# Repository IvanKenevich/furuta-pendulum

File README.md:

# furuta-pendulum

Inverted rotary pendulum

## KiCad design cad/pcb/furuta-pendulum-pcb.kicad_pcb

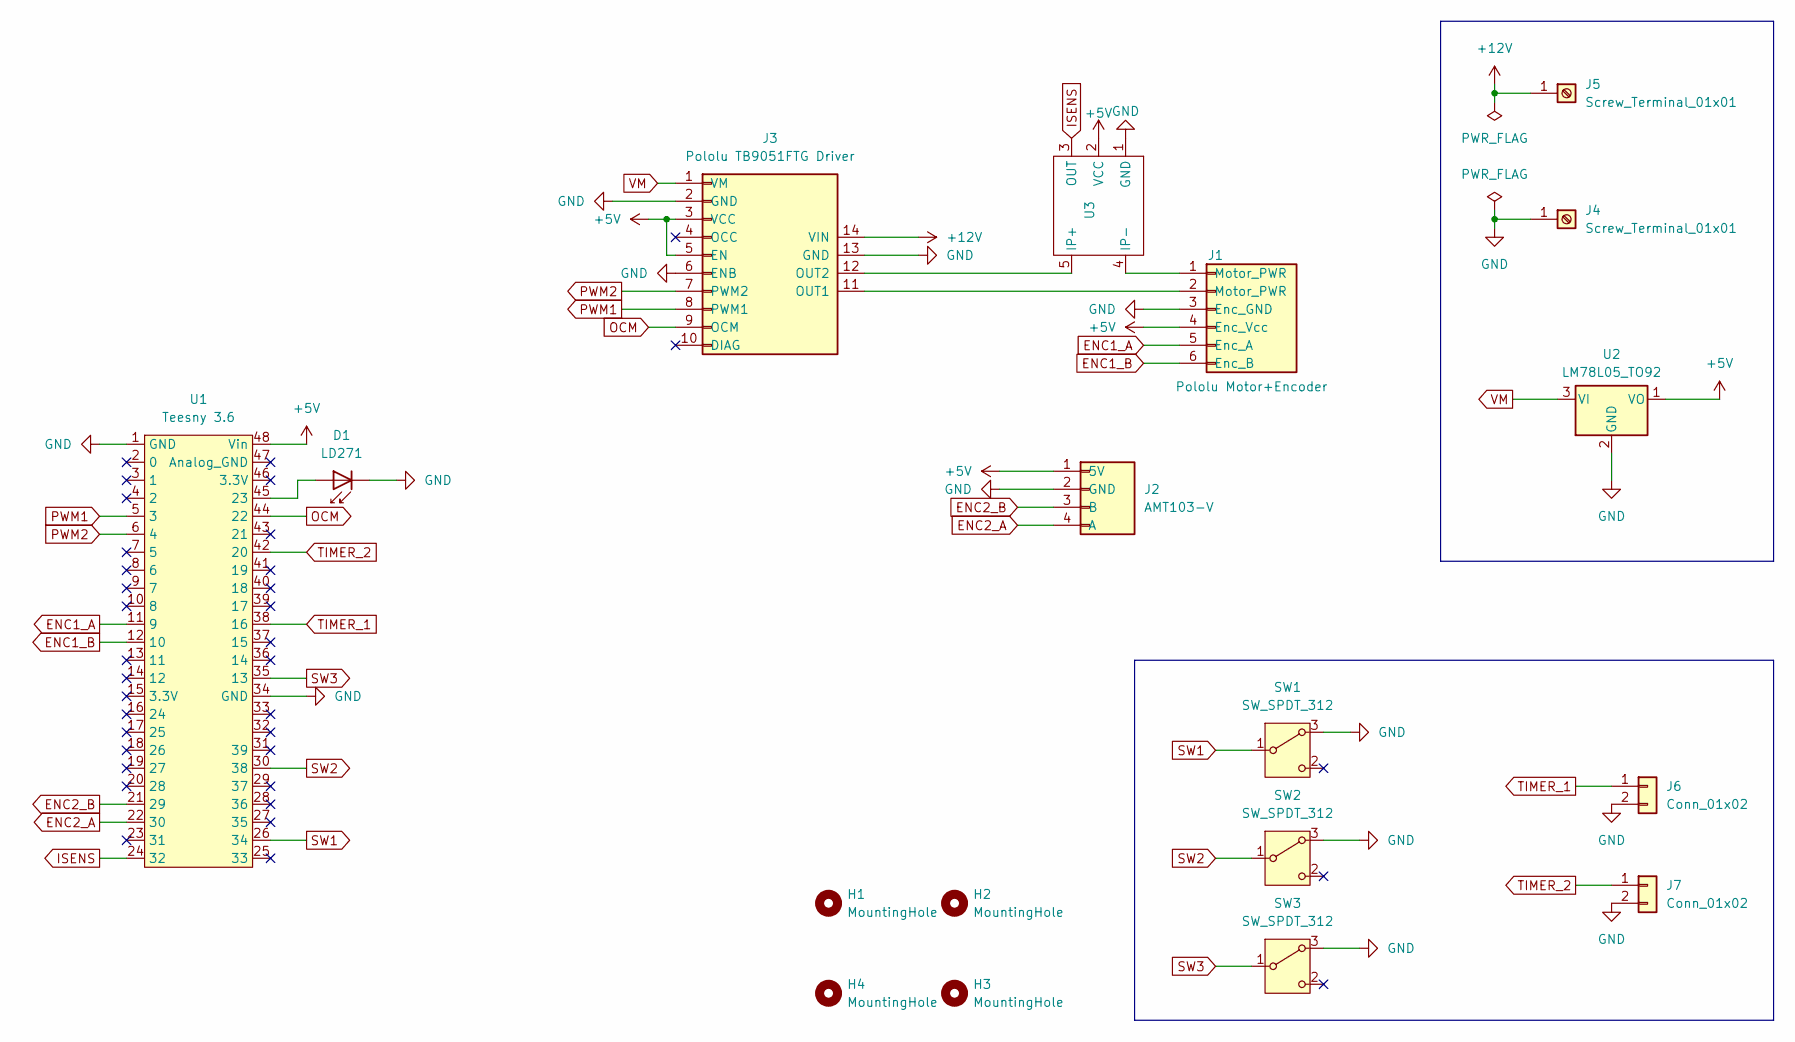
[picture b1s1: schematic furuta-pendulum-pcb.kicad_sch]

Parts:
D1: LD271; LED_D5.0mm_IRGrey
H1, H2, H3, H4: MountingHole; MountingHole_2.2mm_M2
J1: Pololu Motor+Encoder; PinHeader_1x06_P2.54mm_Vertical
J2: AMT103-V; PinSocket_1x04_P2.54mm_Vertical
J3: Pololu TB9051FTG Driver; Pololu TB9051FTG motor driver
J4, J5: Screw_Terminal_01x01; CalTest_CT3151
J6, J7: Conn_01x02; PinHeader_1x02_P2.54mm_Vertical
SW1, SW2, SW3: SW_SPDT_312; Flat Toggle Switch
U1: Teesny 3.6; Teensy 3.6
U2: LM78L05_TO92; TO-92_Inline
U3: Pololu ACS724 Current Sensor

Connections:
+5V: J1.4 (Enc_Vcc), J2.1 (5V), J3.3 (VCC), J3.5 (EN), U1.48 (Vin), U2.1 (VO), U3.2 (VCC)
+12V: J3.14 (VIN), J5.1
ENC1_A: J1.5 (Enc_A), U1.11 (9)
ENC1_B: J1.6 (Enc_B), U1.12 (10)
ENC2_A: J2.4 (A), U1.22 (30)
ENC2_B: J2.3 (B), U1.21 (29)
GND: D1.1 (K), J1.3 (Enc_GND), J2.2 (GND), J3.2 (GND), J3.6 (ENB), J3.13 (GND), J4.1, J6.2, J7.2, SW1.3 (A), SW2.3 (A), SW3.3 (A), U1.1 (GND), U1.34 (GND), U2.2 (GND), U3.1 (GND)
ISENS: U1.24 (32), U3.3 (OUT)
unnamed: D1.2 (A), U1.45 (23)
unnamed: J1.2 (Motor_PWR), J3.11 (OUT1)
unnamed: J3.12 (OUT2), U3.5 (IP+)
unnamed: J1.1 (Motor_PWR), U3.4 (IP-)
OCM: J3.9 (OCM), U1.44 (22)
PWM1: J3.8 (PWM1), U1.5 (3)
PWM2: J3.7 (PWM2), U1.6 (4)
SW1: SW1.1 (B), U1.26 (34)
SW2: SW2.1 (B), U1.30 (38)
SW3: SW3.1 (B), U1.35 (13)
TIMER_1: J6.1, U1.38 (16)
TIMER_2: J7.1, U1.42 (20)
VM: J3.1 (VM), U2.3 (VI)

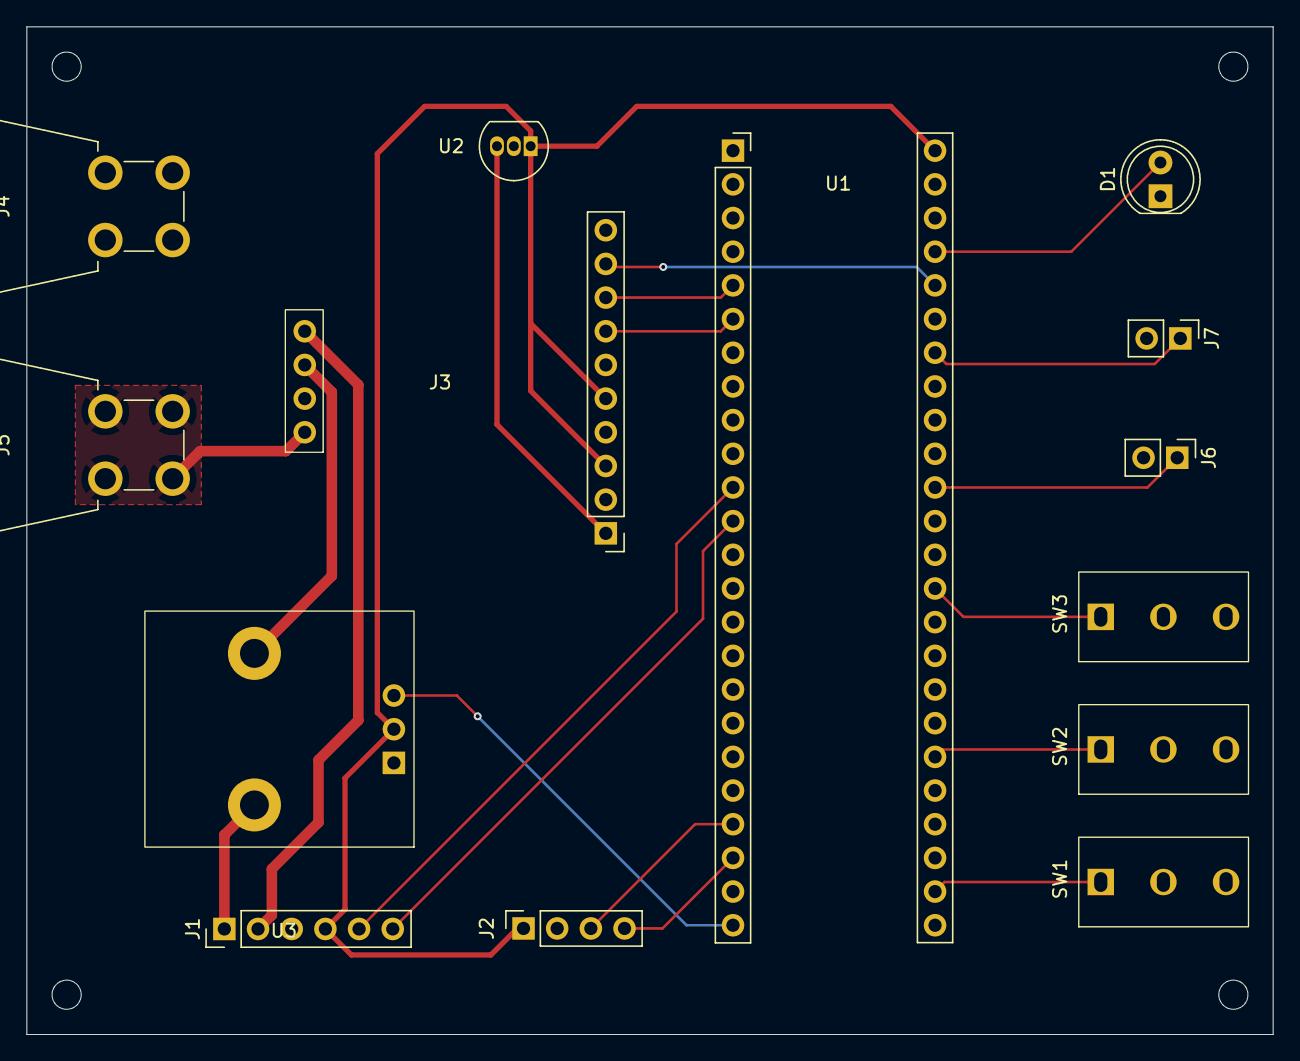
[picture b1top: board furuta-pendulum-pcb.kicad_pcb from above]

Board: 2 copper layers, 94.0 x 76.0 mm, 18 parts (0 on the bottom side), 21 nets.

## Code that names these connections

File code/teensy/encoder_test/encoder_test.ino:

#include <Encoder.h>

#define rad2deg (180.0 / M_PI)
#define deg2rad (M_PI / 180.0)

//#define LED_BUILTIN 13
#define PIN_ENC1_A   2
#define PIN_ENC1_B   3
#define PIN_TIMER_1   32
#define PIN_TIMER_2   31
#define PIN_PWM1    29
#define PIN_PWM2    30
#define PIN_SW_1    33
#define PIN_SW_2    39
#define PIN_SW_3    15

#define TIMER_CYCLE_MICROS 1 * 100
const float Ts = 1e-6 * TIMER_CYCLE_MICROS;
IntervalTimer t1;
const float input_freq = 4, // Hz
            input_amp  = 5, // V
            supply_voltage = 12; // V
const int pos_buff_size = 50; // samples
unsigned long i = 0;

Encoder enc1(PIN_ENC1_A, PIN_ENC1_B),
        enc2(PIN_ENC2_A, PIN_ENC2_B);
volatile long enc1_pos_raw, enc2_pos_raw;
volatile float enc1_pos, enc2_pos, enc2_speed;
float enc2_pos_buff[pos_buff_size] = {0};

volatile char timer1_pin_state = 0, timer2_pin_state = 0;
volatile float pwm_out = 0, pwm_out_copy = 0, error = 0, setpoint = 0, integral = 0;
volatile int motor_enabled = false, integral_enabled = false;


void setup() {
  pinMode(LED_BUILTIN, OUTPUT);
  digitalWrite(LED_BUILTIN, HIGH);

  pinMode(PIN_TIMER_1, OUTPUT);
  pinMode(PIN_TIMER_2, OUTPUT);
  pinMode(PIN_SW_1, INPUT);
  pinMode(PIN_SW_2, INPUT);
  pinMode(PIN_SW_3, INPUT);

  Serial.begin(57600);
  
  t1.begin(isr_t1, TIMER_CYCLE_MICROS);

  digitalWrite(LED_BUILTIN, LOW);
}

void isr_t1(void) {
  enc1_pos_raw = enc1.read(); // pulses
  enc2_pos_raw = enc2.read(); 
  enc1_pos = 360.0 * enc1_pos_raw / 8192.0;  // degrees
  enc2_pos = 360.0 * enc2_pos_raw / 1632.67;

  for (int j = pos_buff_size - 1; j > 0; j--) {
    enc2_pos_buff[j] = enc2_pos_buff[j - 1];
  }
  enc2_pos_buff[0] = enc2_pos;
  enc2_speed = (enc2_pos_buff[0] - enc2_pos_buff[pos_buff_size - 1]) / ((pos_buff_size - 1) * Ts);
  

//  setpoint = 45.0 * sin(input_freq * 2 * M_PI * Ts * i);
//  error = (setpoint - enc2_pos);
//  if (integral_enabled) {
//    integral += error;
//  }
//  else {
//    integral = 0;
//  }
//  pwm_out = error * 1.5 + integral * 0.005;

  setpoint = input_amp * sin(input_freq * 2 * M_PI * Ts * i);
  pwm_out = 100.0 * setpoint / supply_voltage;

  if (motor_enabled) {
    write_pwm(pwm_out);
  } else {
    write_pwm(0);
  }
  ++i;

  digitalWrite(PIN_TIMER_1, timer1_pin_state ^= 1);
}

void write_pwm(float percent) {
  if (percent > 0) {
    analogWrite(PIN_PWM1, map(percent, 0, 100, 0, 256));
    analogWrite(PIN_PWM2, 0);
  }
  else if (percent < 0) {
    analogWrite(PIN_PWM1, 0);
    analogWrite(PIN_PWM2, map(percent, -100, 0, 256, 0));
  }
  else {
    analogWrite(PIN_PWM1, 0);
    analogWrite(PIN_PWM2, 0);
  }
}

void loop() {
  //  noInterrupts();
  //  pwm_out_copy = pwm_out;
  //  interrupts();
  //
  //
  Serial.print(setpoint);
  Serial.print("\t");
//  Serial.print(enc2_pos);
//  Serial.print("\t");
  Serial.println(enc2_speed);


  if (digitalRead(PIN_SW_1) == HIGH) {
    motor_enabled = true;
  } else {
    motor_enabled = false;
  }

  if (digitalRead(PIN_SW_2) == HIGH) {
    integral_enabled = true;
  } else {
    integral_enabled = false;
  }
  
  delay(20);
  digitalWrite(PIN_TIMER_2, timer2_pin_state ^= 1);
}

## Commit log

2023-05-05 add existing files
2023-05-06 add docs, start changing code
2023-05-06 rename encoder_test.ino to motor_id.ino
2023-05-06 add 2D_RWIP.ino
2023-05-06 some code reorganization and cleanup
2023-05-07 reorganize and remove unused code
2023-05-07 switch to elapsedMillis, remove unused code
2023-05-07 add motor datasheet
2023-05-07 remove atmega code examples
2023-05-08 collect motor identification data, move old identification data into separate folder
2023-05-09 add screenshot of extracted amplitudes add started code for TF building
2023-05-10 place all matlab code into a separate folder add Jacob's RWIP matlab code add experimentally determined model transfer function
2023-05-11 add code to simulate damped unpowered arm
2023-05-11 add teensy code to collect arm damping data add first dataset collected from arm
2023-05-13 collect dataset with clip collect info about arm and clip rename original dataset add code to plot simulated on top of real oscillations
2023-05-17 add state-space formulation that includes motor dynamics but with inductance assumed as zero change reference position so that arm 1 doesn't try to go to zero add file with ideas
2023-05-18 add motor dynamics to odefun_torque.m change motor damping and other constants to values from motor id add state-space fomulation that does not ignor inductance minor plotting changes
2023-05-20 add current back into error calculation, change how arm speeds are plotted
2023-05-23 Redesign arm 1 attachment to motor shaft, remove weight savings features, add wire routing hole
2023-05-23 commit the rest of work from last commit
2023-05-23 change top plate design to include recess for nuts
2023-05-24 add bolt holes to arm2, add bolts and nuts through the holes
2023-05-24 add observer design function and a demo of how to use it
2023-05-24 add basic swingup code
2023-05-25 rotate setscrew hole on shaft coupler, add M3-10 bolt, add slot for setscrew in arm1
2023-05-31 add density to most relevant parts (not all yet), make arm2 thicker at the shaft section, add spacer disks between the bearings
2023-06-01 finish adding material properties, make sure materials are stored in the materials.sldmat file, fix reference in arm1 that was causing constant rebuilds
2023-06-01 update arm cg positions, total arm masses, inertia tensors
2023-06-01 re-obtain arm2 dynamic friction coefficient
2023-06-07 - reverse directions for both encoders and the motor so that it matches the sign convention established in the paper - change controller interrupt priority to a lower value to minimize chances of los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
2023-06-07 - collect dataset with step input
2023-06-09 remove old unnecessary files from paper folder, separate controller design and system derivation into separate files
2023-06-09 implement step input simulation based on measured data
2023-06-09 fix bug in derive_coefficients where I1 and I2 had no values defined for substitution, rederive system with simplified inertia, minor improvements to step_input simulation
2023-06-09 add gitignore for MATLAB autosave files
2023-06-10 add more ideas
2023-06-11 collect dataset with a higher voltage step input
2023-06-11 collect dataset with higher frequency step input
2023-06-11 fix Observer bug with C matrix size
2023-06-11 design_controller.m - switch from fully measured system to realistically measured - add observer design and benchmark - move control law into a separate function
    build_ss_models.m
    - switch from simplified to full inertia tensors
    - create version of full system with realistic measurement matrix
2023-06-12 add digital controller design and begin printng C code
2023-06-12 refresh mat file with 4x5 C matrix
2023-06-14 design_controller.m - add code to print C variable definitions - change Observer call to match new signature
    build_ss_models.m
    - comment out the version that saves function handles to get rid of the warning on personal computer when loading mat fie
    Observer.m
    - add explicit handing of observer design for digital systems
    furuta-pendulum.ino
    - add linear algebra implementation of observer and control, still work in progress
2023-06-14 regenerate mat file without symoblic functions in it
2023-06-14 - add swingup timeout logic - add feedback error calculation and reference state
2023-06-15 design_controller.m - place nondominant closed loop poles farther away - zero out arm1 position gains
    build_ss_models.m
    - bring back export of function handles for nonlinear simulation
    derived_systems.mat
    - caused by changes to build_ss_models.m
    test_DigitalObserver.m
    - bring over Turcic's example code
2023-06-15 - fix observer estimation bug where u was used instead of r when multiplying B. Since r is 0, that term can be dropped - remove state 1 reference update since arm1 controller gain will already be set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
2023-06-20 make controller output design to mat file start implementing observer test that uses designed controller
2023-06-20 collect dataset with all of the relevant variables for analysis
2023-06-21 collect dataset2 which is the same controller as dataset1 but with faster printing, add more code to analyze this data
2023-06-21 - collect dataset with improved ICs - collect dataset with improved ICs and V/R current estimation - adjust controller rise time and PMO to make the system reasonably balance
2023-06-21 - ovverride current estimate with V/R - bring swingup back in - reduce max motor voltage - print faster - control gain adjustments because of Tr and PMO changes
2023-08-10 new base design
2023-08-10 - change motor PWM pins to match new layout - change switch pins to match new layout - configure switch pins as pullup - define functions to provide sine and square wave signal sources for testing
2023-08-11 - add new blink LED to replace the one that is used by the switch - add some ideas
2023-08-16 replace motor props with Jacob's motor
2023-08-17 enable arm1 position control, make controller faster
2023-08-17 - increase motor voltage thresholds - convert from Ivan to Jacob's motor (resistance, pulses per rev) - add arm1 position reference adjustment - change swingup algorithm to go in another direction af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
2023-08-19 - organize ideas into sections - add current estimation idea
2023-08-19 add balancing state machine diagram
2023-08-22 furuta-pendulum.ino - change pin for switch 2 (LED pin wasn't working as pullup) and assign that switch to swingup request - add swingup and balancing state machine - implement floored division modul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
    state_machine.drawio
    - add speed threshold check to transition from wait to move right
2023-08-24 - ideas review - add eig and eigv discussion to drawio - add encoder datasheet - use error variable in arduino instead of discarding it
2023-09-08 Redesign arm1 and arm2 to convert bushing+shaft assembly of arm2 into a single ball bearing
2023-09-09 Update all statically determinable system properties for new design (mass, length, inertia)
2023-09-13 obtain new arm2 damping, correct arm2 mass and CG position
2023-09-13 nonfunctional part updates due to soldiworks update
2023-09-15 MathNotWorks (fix subs problem), rederive coefficients and controller params for new design, cross out and add new ideas
2023-09-20 fix bug in Observer.m for digital systems, plot state trajectories instead of measurements from initial()
2023-10-03 furuta_pendulum.ino - fix current observer - fix arm 2 reference - adjust controller pars
    ideas.txt
    - delete because all moved to github issues
    state_machine.drawio
    - observer and controller drawings for learning
2023-10-04 Rewrite digital observer simulation, print out A and C matrices instead of A_1
2023-12-28 build_ss_models.m - add down linearized system to the workspace - add linearized system odefun version for simulation
    design_controller.m
    - add comparison between linearized and nonlinearized system (for easing
    future simulation)
2025-07-18 test commit
2025-07-25 Start pcb development
2025-07-25 Add note that version 3.7 of BLA library is required
2025-10-15 update pcb files
2025-10-15 add current sensor breakout board
2025-10-16 create pcb traces, add mounting holes
2025-10-21 remove unused symbol libraries
2025-10-21 add notebook for pcb calculations
2025-10-28 complete 5V current and power calculator
2025-12-10 board updates
2025-12-18 heatsink sizing math, small schematic renames and moves
2026-02-10 cleanup files
2026-02-10 final cleanup
2026-03-03 add more info sources, raise heatsink math ambient temp to 100F
2026-03-24 add more regulator heat sink calculations
